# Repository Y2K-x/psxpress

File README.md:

# PSXpress
A compact handheld PlayStation console using original PS1 hardware.

## Scope
This end goal of this project is to create a compact PS1 portable using modern portablizing techniques. A special motherboard trim for PU-23 units is being developed that leverages the CD subsystem emulation capabilities of the PSIO ODE. Using PSIO, a trim size of roughly 80mm<sup>2</sup> is achievable, making it the smallest PS1 trim that has been concieved.

Currently, this first iteration of PSXpress is being designed for the [BitBuilt 2023 Summer Build Competition](https://bitbuilt.net/forums/index.php?threads/bitbuilts-2023-summer-building-competition.5710/), however I have plans to continue it further, gradually refining the design to become a highly integrated build using a fully custom motherboard. This has multiple advantages, but will take a long time to complete. The first iteration of the build will be using standard motherboard trimming techniques & a modular design with hand wired relocations.

The ultimate purpose of this project is to forward my electronics design learning goals & to create a build that encorporates the best techniques that the portablizing community has to offer.

## Progress
Currently, the first iteration of the system has yet to be completed. The hope was to have it completed for the BitBuilt Summer Build Competition deadline on October 1st, however that unfortunately does not seem like it will happen. Regardless, I have made a considerable amount of progress and fully intend on seeing this build through to the end.

As of now, I have finished these parts of the build:
- Trim development - the trim layout has been finalized and all relocations have been mapped out to be within the trim area
- Video DAC Relocation - the Video DAC on the PS1 needs to be relocated in order to be within the trim area. I have developed a PCB that accepts the VDAC chip and outputs a clean RGBs signal.
- Power Management - For a portable build, a compact and efficient power management solution is key. I have developed a small 3cm * 2cm board that accepts a 12V DC input and can charge 18650/21700 lithium batteries in a 1S setup. This power management system also has 2 on board 2A voltage regulators for a 3v5 rail (main PS1 system power) and a 5V rail for peripherals & other things.

These are the parts of the project that need to be completed still:
- Case design: I have a rough idea on the layout of the build, but I have been holding off on 3D CAD work until I can prove that the trim itself will work how I want it to
- The trim + relocations: While the trim layout is completed, I still need to perform all the relocations & actually trim the board. The VDAC relocation is done and installed, and I have tested the BIOS and PSIO relocation, however the final relocations have yet to be performed.
- Controller emulation: I am looking into emulating a PS1 controller & memory card using the RP2040 microcontroller. I'm basing the code off the [PicoMemcard](https://github.com/dangiu/PicoMemcard) firmware, which is a fully featured memory card emulator for the PS1. I've done all the coding for it but I have yet to properly test it.
- Audio DAC & Amp: I will be using the [4LayerTech U-AMP 2](https://4layertech.com/products/u-amp-2) as the audio DAC and amplifier. This tiny board provides high quality audio output from digital & analog audio sources, however its firmware needs to be modified to support the PS1. I have made the necessary modifications to the code but have not tested it yet. If I can get this working, I will be working with the 4LayerTech team to add proper PS1 support to the product.
- Final assembly, obviously.

I'd say I'm approaching the 50% completion mark, but there still a lot more to be done.

## Repository Contents
Currently this repository contains some of the research material, documentation, and design files I've been working on, but not all, since many of them are still in a state that I don't feel comfortable sharing yet. Here is the layout of the repo as it currently stands.

### PCB files & CAD (/CAD)
This folder contains all CAD & PCB design files for this project. Please see below for more details on each subfolder.

#### PSXpress PMS (/CAD/PCB/psxpress-pms)
*All files in this folder are licensed under the TAPR Open Hardware License. Please see /CAD/PCB/psxpress-pms/LICENSE.txt for more information.*

This folder contains the design docs for the PSXpress Power Management System (PMS). It's functionality is as follows:
- Fully standalone design: no MCU or firmware to program, just assemble and go
- 3.9 to 13.5V input - 3A max input & charge current - good for 9/12V @ 3A USB-C PD or barrel jack input
- High efficiency 3v5 & 5V buck/boost regulators
- 2A max output on output rails
- Charge & play support
- Integrated battery management & charging
- 1S Battery Setups Only! Recommended setup is 1S2P 18650 cells or 1 21700 cell - I probably wouldn't do a singular 18650 since this will always charge the batteries at 3A no matter what
- Reverse battery polarity protection (separate packside protection circuit needed, example [here](https://www.aliexpress.us/item/3256805302254769.html))
- Soft power switch using MAX16054 - use a normally open SPST switch
- Charging LED
- Dimensions : Aprox. 25mm x 30mm

This board has been designed to be manufactured by DKRed. JLCPCB/PCBWay should also be able to manufacture these boards as well if you want to give them a try, but I cannot make any guarantees. I am not confident that OSH Park can manufacure these boards as they are quite small and detailed.

#### Video DAC Relocation (/CAD/PCB/pu-23\_VDAC\_reloc)
*All files in this folder are licensed under the TAPR Open Hardware License. Please see /CAD/PCB/pu-23_VDAC_reloc/LICENSE.txt for more information.*

This folder contains the design docs for the PSXpress Video DAC relocation board. It's functionality is as follows:
- Accepts a PU-23 Video DAC IC
- Takes in the PS1's 24bit digital video bus and outputs clean RGB with Composite Sync
- Generates a composite sync signal from the PS1's Sync on Luma signal, since tapping into the standard CSync signal the PS1 generates messes up the VDAC output.
  - The use of CSync on this board is not required, as the PS1 also outputs a H/V sync signal off the GPU if you would prefer to use that. I have not tested it, but that may be more useful if you intend on hooking up the PS1 directly to a VGA display driver board.
  - The generated CSync signal has been confirmed to work with the GBS-Control scaler (more specifically, [Shinobi Scaler by YveltalGriffin](https://github.com/mackieks/Shinobi-Scaler). I have not tested it with other scalers or directly with display drivers that accept CSync.

Please note: the PCB itself does not have any silkscreen markings for the pinout of the solder pads on it's edge. Please see the kicad pcb file for that information. I will document this more properly later on, or I might try and figure out a way to include the pinout markings on the PCB itself in the future.

This board has been designed to be manufactured by JLCPCB. PCBWay should also be able to fabricate this. DKRed cannot by default since this board is 0.8mm thick, but honestly there is no reason why this needs to be 0.8mm, I was just trying to keep the relocation stack-up as thin as possible. 1.6mm should be fine if you want to have DKRed fabricate this, assuming it's within their size tollerances. OSH Park may also be able to fabricate this using their 0.8mm 2oz service, but I cannot make any guarantees here.

#### All-in-One Relocation Flex PCB (/CAD/PCB/relocation-flex)
*All files in this folder are licensed under the TAPR Open Hardware License. Please see /CAD/PCB/relocation-flex/LICENSE.txt for more information.*

This folder contains the design docs for the PSXpress All-in-One relocation flex PCB. It is currently a WIP.

This design will combine all the hand wired relocations into one easy to install flex board. The first iteration will handle the BIOS, PU-18 SPU, and VDAC relocations and eliminate the need for handmade fly-wire relocations, significantly lowering the skill ceiling required to build a PU-23 based PS1 portable. Future iterations may eliminate the PU-18 SPU entirely for an accurately emulated replacement solution. I may also look into utilizing a flash chip to contain the BIOS ROM, which will allow you to use an alternative ROM of your choosing, or possibily include multiple banks of ROMs that you can swap between. A flash based solution would also allow for the use of a smaller footprint chip, making the flex PCB smaller in size. Another option down the road could be to use a MCU like the RP2040 or FPGA/CPLD as a "ROMulator" of sorts.

The development of the AIO Relocation Flex will remain on its own separate branch until it's in a completed state, which it will then be upstreamed into the main branch. Please note that the design in this branch will likely not be fully functional for quite a while, and is only updated regularly to document the design process.

#### PSIO to FFC Adapter QSB (/CAD/PCB/psio-qsb)
*All files in this folder are licensed under the TAPR Open Hardware License. Please see /CAD/PCB/psio-qsb/LICENSE.txt for more information.*

This folder contains the design docs for the PSIO to flat-flex cable (FFC) quick solder board (QSB).

This design assists in interfacing a PSIO to the All-in-One Relocation Flex PCB without having to run a bunch of wires between the two. Simply solder the QSB to the PSIO and connect the two with a standard 40pin 0.5mm pitch FFC, preferably one that is as short as possible to not have to worry about the excess cable length. This cable will also run power from the PS1 to the PSIO, so you do not have to worry about wiring power separately. You will have to modify the PSIO to accept 3v5 power instead of 7v5. I will create a diagram that shows exactly what needs to be done at some point.

The PSIO QSB will remain on the relocation-flex branch until the AIO Relocation Flex is in a completed state, which it will then be upstreamed into the main branch.

### Research Documentation (/Documentation)
*All files in this folder are licensed under the public domain (Creative Commons CC0 in technicality). Please see /Documentation/LICENSE.txt for more information.*

This folder contains all the research documentation that I have created, and also will contain a list of further docs that I used to create this project once I get around to compiling that information. Currently, it contains:

- PU-18 SPU Relocation Pin Mapping (pu18-spu-mapping.png): Currently, in order to achieve the small trim, the SPU from a PU-18 motherboard will have to be frankenstein'd onto the board. I have mapped out all the required signals in order to perform this relocation. One can trim a PU-18 board to remove the section of the board that this image covers. Treat the cropping of the image as the trim lines for the board. I will eventually be looking into a SPU replacement so that sacrificing 2 PS1 systems will not be required.

### Logos & Other Artistic Works (/Logos)
*All files in this folder are licensed under the Creative Commons CC BY-SA License. Please see /Logos/LICENSE.txt for more information.*

This folder contains the logo design that I created for this project. I've included PNGs and an SVG of the logo. This logo is also used in the CAD files and other documentation.

## Special Thanks
I'd like to give a special thanks to the following communities and persons for all their support with this project so far:

- [BitBuilt](https://bitbuilt.net/) & its [Discord server](https://discord.com/invite/6z8FSv8B)
- [PSX.dev](https://discord.gg/QByKPpH)
- [ReSwitched](https://discord.gg/ZdqEhed)
- [YveltalGriffin](https://github.com/mackieks)
- [Gmanmodz](https://github.com/Gmanmodz)
- [Aurelio](https://github.com/Aurelio92)

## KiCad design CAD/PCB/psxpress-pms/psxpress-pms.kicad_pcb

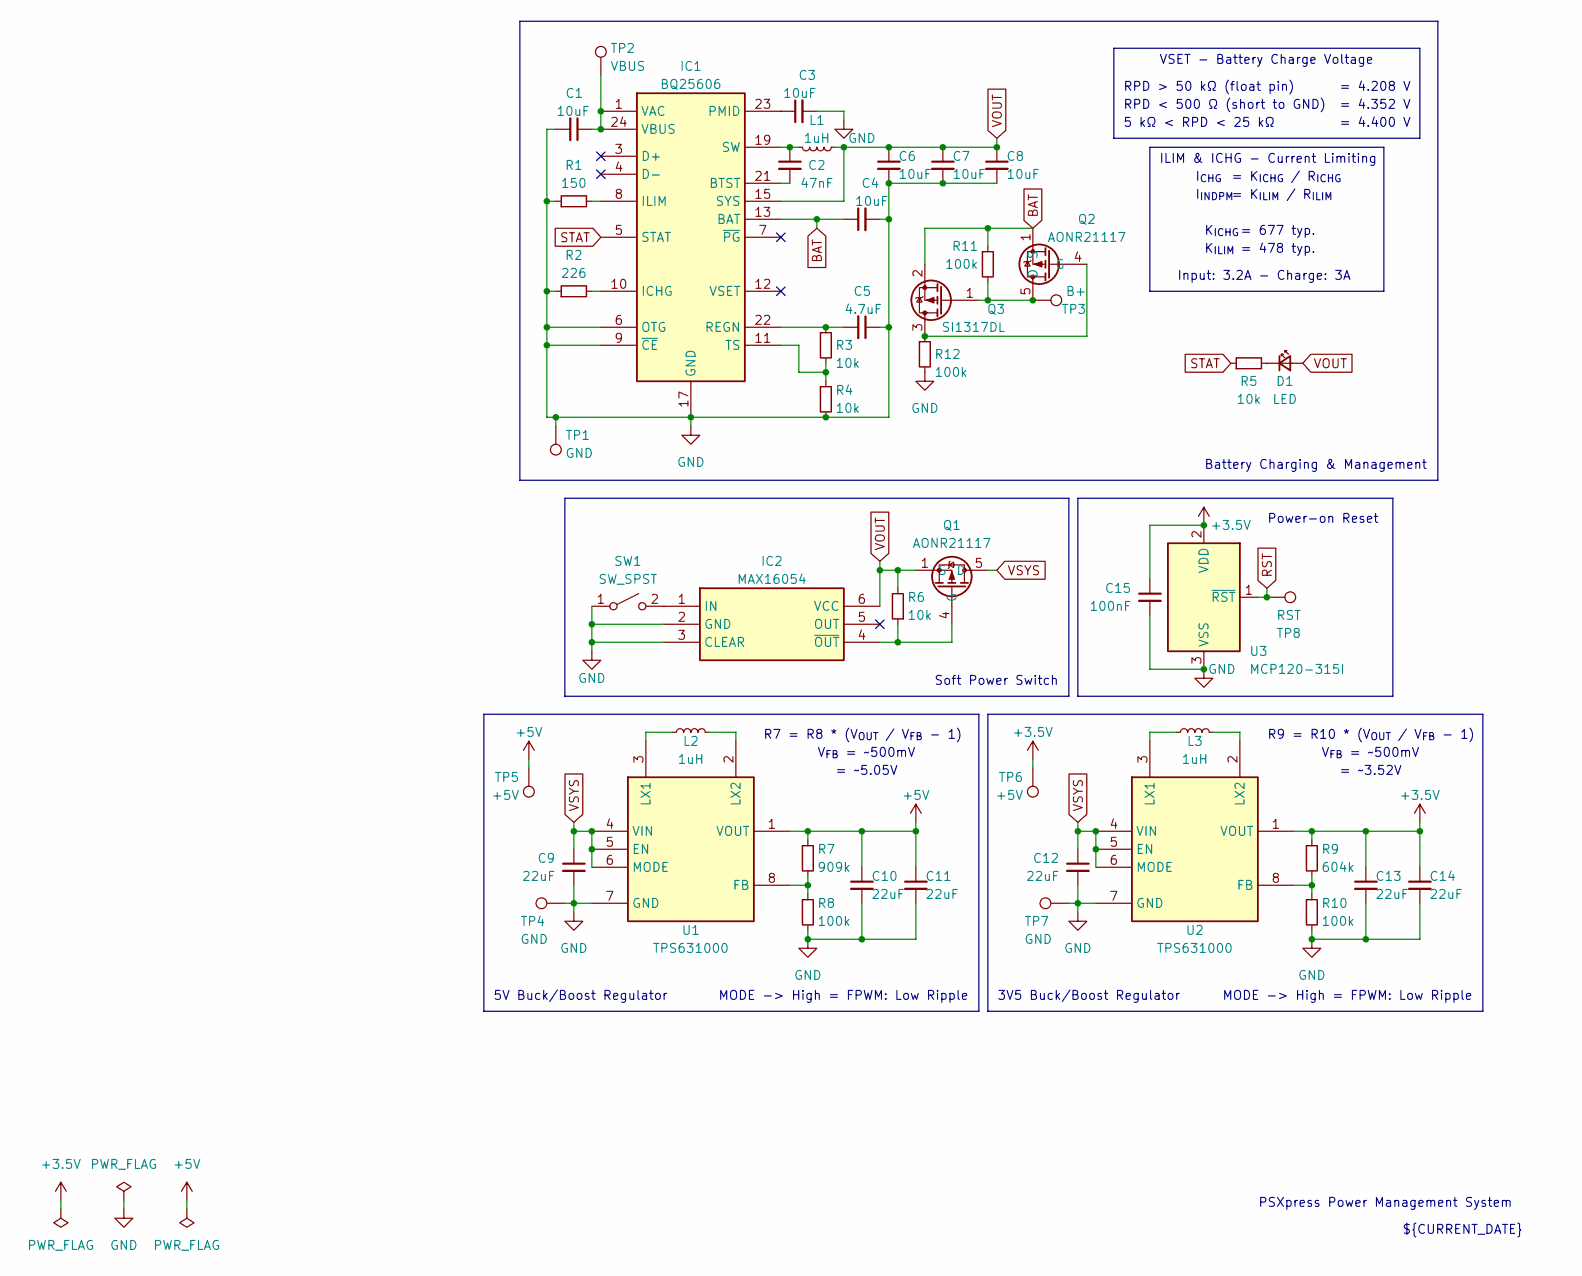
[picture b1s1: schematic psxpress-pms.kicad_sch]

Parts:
C1, C3, C4, C6, C7, C8: 10uF; C_0805_2012Metric
C2: 47nF; C_0805_2012Metric
C5: 4.7uF; C_0805_2012Metric
C9, C10, C11, C12, C13, C14: 22uF; C_0805_2012Metric
C15: 100nF; C_0603_1608Metric
D1: LED; led_1.25mm_2
IC1: BQ25606; QFN50P400X400X100-25N-D; Mouser Part Number 595-BQ25606RGER
IC2: MAX16054; SOT95P275X110-6N; Mouser Part Number 700-MAX16054AZTT
L1, L2, L3: 1uH; L_Taiyo-Yuden_MD-4040
Q1, Q2: AONR21117; TRANS_AONR21321
Q3: SI1317DL; SOT-323_SC-70
R1: 150; R_0603_1608Metric
R2: 226; R_0603_1608Metric
R3, R4, R5, R6: 10k; R_0603_1608Metric
R7: 909k; R_0603_1608Metric
R8, R10: 100k; R_0603_1608Metric
R9: 604k; R_0603_1608Metric
R11, R12: 100k; R_0402_1005Metric
SW1: SW_SPST; pwr_switch_1.25mm_2
TP1, TP4, TP7: GND; hipower_2.5x1.5mm
TP2: VBUS; hipower_2.5x1.5mm
TP3: B+; hipower_2.5x1.5mm
TP5, TP6: +5V; hipower_2.5x1.5mm
TP8: RST; lopower_1.25mm
U1, U2: TPS631000; SOT-583-8; Mouser Part Number 595-TPS631000DRLR
U3: MCP120-315I; SOT-23

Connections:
+3.5V: C13.1, C14.1, C15.1, R9.1, TP6.1, U2.1 (VOUT), U3.2 (VDD)
+5V: C10.1, C11.1, R7.1, TP5.1, U1.1 (VOUT)
BAT: C4.1, IC1.13 (BAT), IC1.14 (BAT), Q2.1 (S), Q2.2 (S), Q2.3 (S), Q3.2 (S), R11.1
GND: C1.2, C3.2, C4.2, C5.1, C6.2, C7.2, C8.2, C9.2, C10.2, C11.2, C12.2, C13.2, C14.2, C15.2, IC1.6 (OTG), IC1.9 (~CE), IC1.17 (GND), IC1.18 (GND), IC1.25 (GND), IC2.2 (GND), IC2.3 (CLEAR), R1.1, R2.1, R4.2, R8.2, R10.2, R12.2, SW1.1 (A), TP1.1, TP4.1, TP7.1, U1.7 (GND), U2.7 (GND), U3.3 (VSS)
unnamed: C2.1, IC1.19 (SW), IC1.20 (SW), L1.2
unnamed: D1.1 (K), R5.2
unnamed: C2.2, IC1.21 (BTST)
unnamed: IC1.10 (ICHG), R2.2
unnamed: IC1.8 (ILIM), R1.2
unnamed: C3.1, IC1.23 (PMID)
unnamed: C5.2, IC1.22 (REGN), R3.1
unnamed: IC1.11 (TS), R3.2, R4.1
unnamed: C1.1, IC1.1 (VAC), IC1.24 (VBUS), TP2.1
unnamed: IC2.1 (IN), SW1.2 (B)
unnamed: IC2.4 (~OUT), Q1.4 (G), R6.1
unnamed: Q2.4 (G), Q3.3 (D), R12.1
unnamed: Q2.5 (D), Q2.6 (D), Q2.7 (D), Q2.8 (D), Q2.9 (D), Q2.9_1 (D), Q2.9_2 (D), Q3.1 (G), R11.2, TP3.1
unnamed: R7.2, R8.1, U1.8 (FB)
unnamed: L2.1, U1.3 (LX1)
unnamed: L2.2, U1.2 (LX2)
unnamed: R9.2, R10.1, U2.8 (FB)
unnamed: L3.1, U2.3 (LX1)
unnamed: L3.2, U2.2 (LX2)
RST: TP8.1, U3.1 (~RST)
STAT: IC1.5 (STAT), R5.1
VOUT: C6.1, C7.1, C8.1, D1.2 (A), IC1.15 (SYS), IC1.16 (SYS), IC2.6 (VCC), L1.1, Q1.1 (S), Q1.2 (S), Q1.3 (S), R6.2
VSYS: C9.1, C12.1, Q1.5 (D), Q1.6 (D), Q1.7 (D), Q1.8 (D), Q1.9 (D), Q1.9_1 (D), Q1.9_2 (D), U1.4 (VIN), U1.5 (EN), U1.6 (MODE), U2.4 (VIN), U2.5 (EN), U2.6 (MODE)

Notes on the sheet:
= ~5.05V
V_{FB} = ~500mV
MODE -> High = FPWM: Low Ripple
R7 = R8 * (V_{OUT} / V_{FB} - 1)
K_{ICHG}
Soft Power Switch
= ~3.52V
= 478 typ.
5V Buck/Boost Regulator
= K_{ICHG} / R_{ICHG}
RPD > 50 kΩ (float pin)
= K_{ILIM} / R_{ILIM}
ILIM & ICHG - Current Limiting
3V5 Buck/Boost Regulator
RPD < 500 Ω (short to GND)
= 4.208 V
= 4.400 V
Input: 3.2A - Charge: 3A
Battery Charging & Management
Power-on Reset
PSXpress Power Management System
I_{INDPM}
K_{ILIM}
5 kΩ < RPD < 25 kΩ
I_{CHG}
VSET - Battery Charge Voltage
= 677 typ.
R9 = R10 * (V_{OUT} / V_{FB} - 1)
= 4.352 V
${CURRENT_DATE}

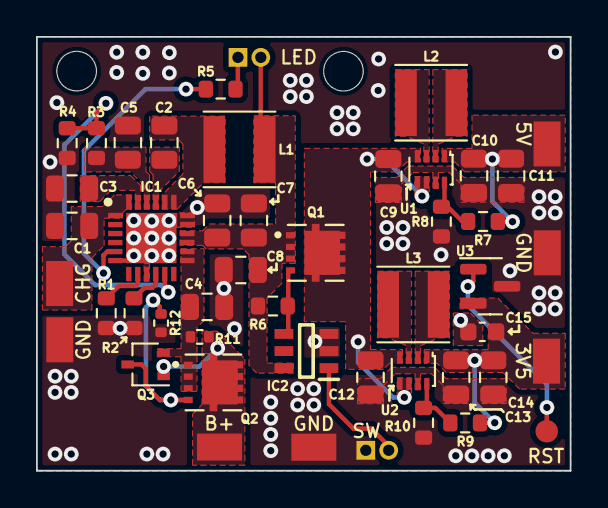
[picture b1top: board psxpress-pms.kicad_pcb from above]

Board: 2 copper layers, 29.7 x 24.1 mm, 48 parts (0 on the bottom side), 27 nets.

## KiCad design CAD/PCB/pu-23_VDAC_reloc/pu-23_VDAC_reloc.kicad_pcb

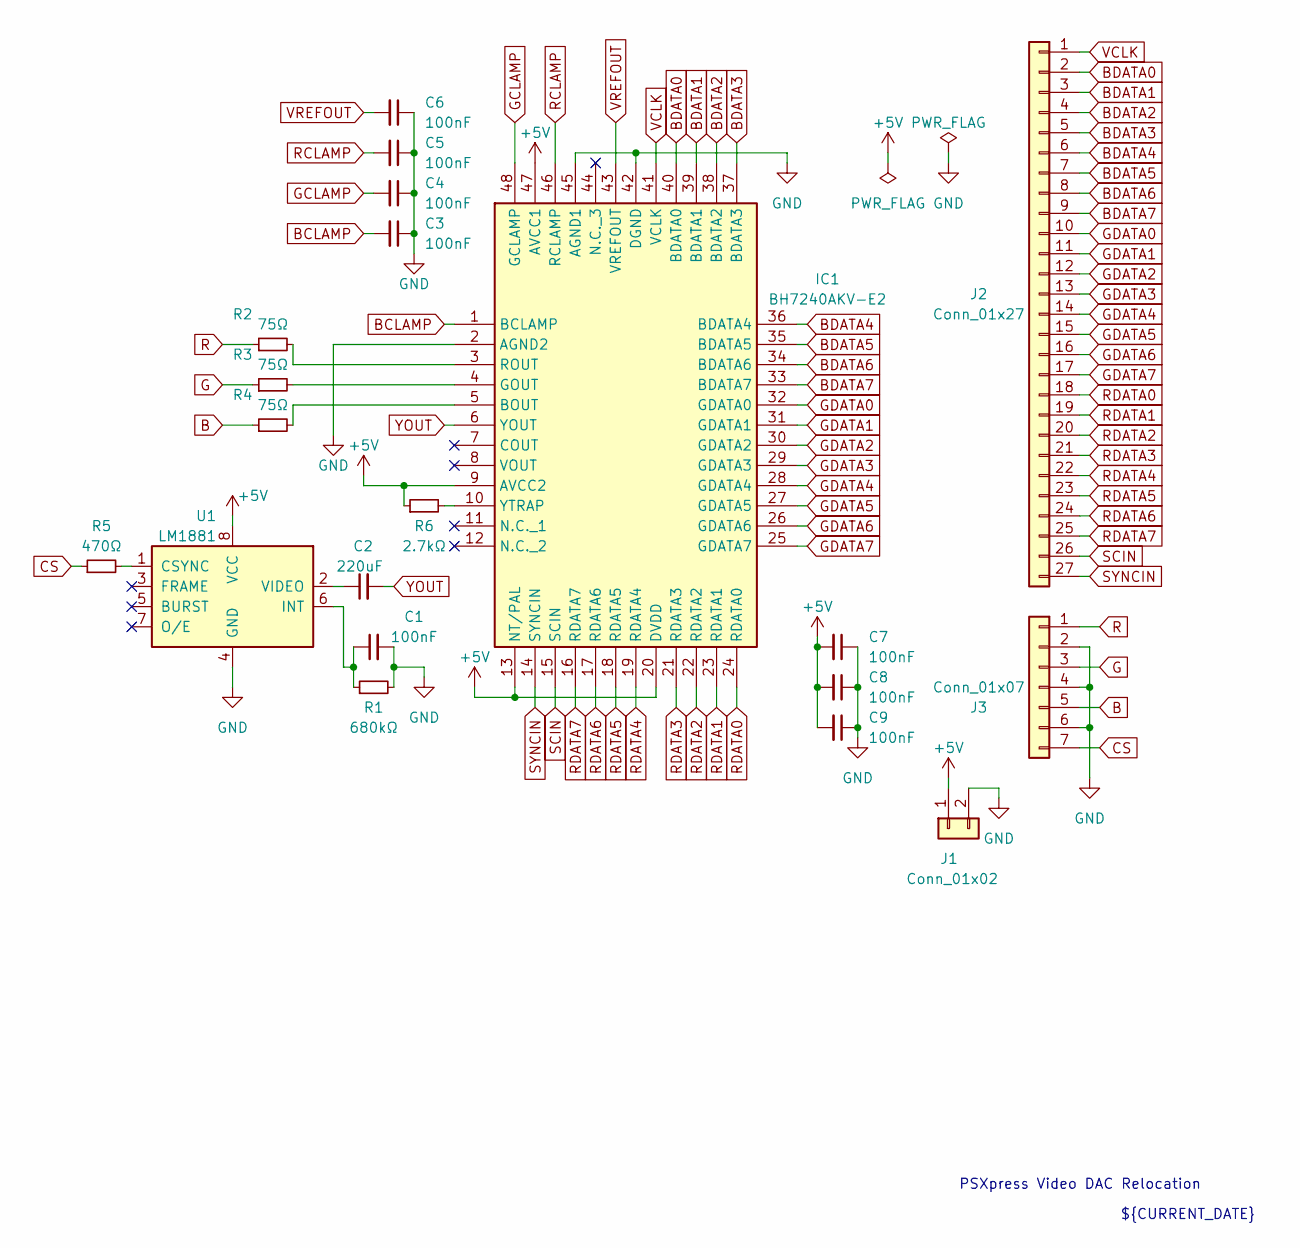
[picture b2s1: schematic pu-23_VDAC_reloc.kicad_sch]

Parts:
C1, C3, C4, C5, C6, C7, C8, C9: 100nF; C_0603_1608Metric
C2: 220uF; C_0603_1608Metric
IC1: BH7240AKV-E2; QFP50P900X900X160-48N; Mouser Part Number 755-BH7240AKV-E2
J1: Conn_01x02; POWER_IN
J2: Conn_01x27; DIGITAL_RGB_PADS
J3: Conn_01x07; ANALOG_RGB_PADS
R1: 680kΩ; R_0603_1608Metric
R2, R3, R4: 75Ω; R_0603_1608Metric
R5: 470Ω; R_0603_1608Metric
R6: 2.7kΩ; R_0603_1608Metric
U1: LM1881; SOIC-8_3.9x4.9mm_P1.27mm

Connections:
+5V: C7.2, C8.2, C9.2, IC1.9 (AVCC2), IC1.13 (NT/PAL), IC1.20 (DVDD), IC1.47 (AVCC1), J1.1, R6.1, U1.8 (VCC)
B: J3.5, R4.1
BCLAMP: C3.2, IC1.1 (BCLAMP)
BDATA0: IC1.40 (BDATA0), J2.2
BDATA1: IC1.39 (BDATA1), J2.3
BDATA2: IC1.38 (BDATA2), J2.4
BDATA3: IC1.37 (BDATA3), J2.5
BDATA4: IC1.36 (BDATA4), J2.6
BDATA5: IC1.35 (BDATA5), J2.7
BDATA6: IC1.34 (BDATA6), J2.8
BDATA7: IC1.33 (BDATA7), J2.9
CS: J3.7, R5.1
G: J3.3, R3.1
GCLAMP: C4.2, IC1.48 (GCLAMP)
GDATA0: IC1.32 (GDATA0), J2.10
GDATA1: IC1.31 (GDATA1), J2.11
GDATA2: IC1.30 (GDATA2), J2.12
GDATA3: IC1.29 (GDATA3), J2.13
GDATA4: IC1.28 (GDATA4), J2.14
GDATA5: IC1.27 (GDATA5), J2.15
GDATA6: IC1.26 (GDATA6), J2.16
GDATA7: IC1.25 (GDATA7), J2.17
GND: C1.2, C3.1, C4.1, C5.1, C6.1, C7.1, C8.1, C9.1, IC1.2 (AGND2), IC1.42 (DGND), IC1.45 (AGND1), J1.2, J3.2, J3.4, J3.6, R1.2, U1.4 (GND)
unnamed: IC1.5 (BOUT), R4.2
unnamed: IC1.4 (GOUT), R3.2
unnamed: IC1.3 (ROUT), R2.2
unnamed: IC1.10 (YTRAP), R6.2
unnamed: R5.2, U1.1 (CSYNC)
unnamed: C1.1, R1.1, U1.6 (INT)
unnamed: C2.1, U1.2 (VIDEO)
R: J3.1, R2.1
RCLAMP: C5.2, IC1.46 (RCLAMP)
RDATA0: IC1.24 (RDATA0), J2.18
RDATA1: IC1.23 (RDATA1), J2.19
RDATA2: IC1.22 (RDATA2), J2.20
RDATA3: IC1.21 (RDATA3), J2.21
RDATA4: IC1.19 (RDATA4), J2.22
RDATA5: IC1.18 (RDATA5), J2.23
RDATA6: IC1.17 (RDATA6), J2.24
RDATA7: IC1.16 (RDATA7), J2.25
SCIN: IC1.15 (SCIN), J2.26
SYNCIN: IC1.14 (SYNCIN), J2.27
VCLK: IC1.41 (VCLK), J2.1
VREFOUT: C6.2, IC1.43 (VREFOUT)
YOUT: C2.2, IC1.6 (YOUT)

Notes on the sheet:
${CURRENT_DATE}
PSXpress Video DAC Relocation

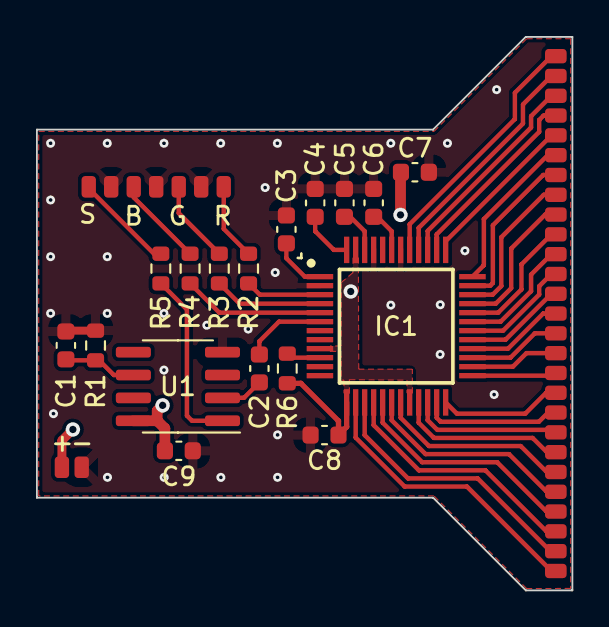
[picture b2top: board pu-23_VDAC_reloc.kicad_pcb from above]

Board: 2 copper layers, 29.8 x 30.7 mm, 20 parts (0 on the bottom side), 45 nets.

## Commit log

2023-07-18 add video dac relocation PCB files
2023-07-18 updated vdac board BOM
2023-07-18 update vdac board gerbers & remove backup files
2023-07-20 add initial pms files
2023-07-20 add kicad gitignore
2023-07-20 pms - add MAX16054 library
2023-07-20 pms - finish battery management circuit & add soft power switch circuit
2023-07-20 pms - actually add the soft power switch circuit this time -.-
2023-07-20 pms - add logo & design info to schematic
2023-07-20 pms - add dcdc regulator libraries
2023-07-20 pms - add dcdc regulator circuits & tidy schematic
2023-07-20 pms - forgot to save again
2023-07-21 pms - switch soft power mosfet to AONR21117 - schematic finished
2023-07-25 pms - add custom power symbol library
2023-07-25 pms - update schematic with footprint assignments + add output rail power symbols
2023-07-25 pms - begin routing - 5V & 3v5 regulators routed
2023-07-25 pms - I really need to make sure to save these dang files before pushing changes.
2023-07-25 pms - add solder pad library
2023-07-25 pms - add voltage reg solder pads + preliminary board edge cuts
2023-07-25 pms - optimize regulator layout & add 3D models for inductors
2023-07-26 pms - route BQ chip, finalize board footprint, & start optimizing
2023-07-27 pms - finish optimizing - board complete
2023-07-27 pms - add preliminary BOM - need to switch some components with better rated ones
2023-08-01 pms - clean up silkscreen, fix solderpad footprints having paste, generate gerbers
2023-08-01 update PCB & gerbers for DKRed
2023-08-01 pms - update 3v5 regulator symbol & fix routing, symbol was incorrect
2023-08-01 pms - update schematic with fixed TPS564255 symbol
2023-08-17 pms - switch from separate buck & boost regs to buck/boost - add todo to schematic - finish buck/boost reg schematic
2023-08-17 pms - add power-on reset circuit schematic
2023-08-17 pms - update schematic todo
2023-08-22 pms - finish routing new regs + POR circuit - add special thanks - awaiting cleanup
2023-08-23 pms - add reverse polarity protection schematic
2023-08-23 pms - route reverse polarity protection circuit, finish cleanup
2023-08-24 pms - clear all DRC errors, further cleanup
2023-08-26 pms - update BOM & gerbers
2023-09-16 relicence PCB design files from GPLv3 to TAPR open hardware license
2023-09-16 add preliminary documentation files (currently just pu-18 spu pin mapping)
2023-09-16 add documentation CC0 license
2023-09-16 add logos
2023-09-16 add logo license
2023-09-16 add scaled down logo for the repo readme and update readme to point to it
2023-09-16 update readme to point to relative path for scaled logo - hope this actually works this time
2023-09-16 fix linking typo in README
2023-09-26 add initial relocation flex files
2023-09-26 reloc-flex: copy over vdac relocation schematic & add symbols for FPC connector & via connections
2023-10-03 reloc - finish BIOS relocation schematic & begin SPU relocation schematic
2023-10-03 reloc - finish SPU relocation schematic
2023-10-05 add PSIO Adapter QSB files - schematic completed, begin routing PCB
2023-10-06 reloc - further routing of psio qsb
2023-10-09 reloc - finish routing psio qsb
2023-10-10 reloc - clean up psio-qsb design
2023-10-10 reloc - finish flex schematic and add finishing touches to psio qsb
2023-10-12 reloc - generate gerbers & create bom for psio qsb
